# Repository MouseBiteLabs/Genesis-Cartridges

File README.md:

# Genesis-Cartridges
A collection of Genesis/Mega Drive cartridge circuit boards

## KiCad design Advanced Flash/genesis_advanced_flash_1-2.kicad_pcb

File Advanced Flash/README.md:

# Genesis / Mega Drive Advanced Flash Cart

This is a Sega Genesis/Mega Drive cartridge circuit board design that is capable of being flashed via the <a href="https://github.com/sanni/cartreader">Open Source Cart Reader (OSCR) by sanni</a>. Alternatively, you can also flash the ROM chips before soldering them to the board through the use of a programmer like the <a href="https://xgecu.myshopify.com/products/xgecu-new-t48-tl866-3gprogrammer-v12-01-support-28000-ics-for-spi-nor-nand-flash-emmc-bga153-162-169-100-221-tsop-sop-plcc">T48 programmer</a> with the <a href="https://xgecu.myshopify.com/products/100-original-xgecu-adp_f48_ex-1-tsop48-special-adapter-for-nor-flash-only-use-on-t48-tl866-3g-programmer">TSOP48 adapter</a>. This cartridge is made entirely from **brand new off the shelf components.** No donors are required, and you don't need to rely on AliExpress or eBay for parts!

This cartridge covers over 95% of the entire Genesis library. You can backup games up to 4 MB in size, with up to 32 KB RAM. It can also handle any ROM hack that falls into these limits, including the ever popular <a href="https://info.sonicretro.org/Sonic_3_Complete">Sonic 3 Complete</a>. Check out the <a href="https://github.com/MouseBiteLabs/Genesis-Cartridges/wiki/Game-Compatibility">Game Compatibility</a> page in the wiki for more info.

All gerbers and source files can be found in this repo, as this project is fully open source. Please read all instructions before attempting the project.

## Pending Version Update

Currently, v1.2 is available for download. It should operate exactly the same as v1.1, but I have not personally verified the new design yet as I have not ordered boards to try them out. The change to v1.2 is to allow these boards to be flashed with the OSCR as 32X cartridges, **but they will still be usable as regular Genesis/Mega Drive cartridges!** No new components have been added, it only needed a simple rewiring of an unused portion of U3.

I do not own a 32X to test this feature out, so if you would like to test out v1.2 for me with a 32X, feel free and let me know your results. Once I verify that my changes do not affect Genesis/Mega Drive compatibility (and they should not!) I will fully update everything here to assume v1.2 is the default version going forward.

For now, **v1.1 is perfectly acceptable for Genesis/Mega Drive games.**

## Important Things Before You Start

1) <a href="https://github.com/MouseBiteLabs/Genesis-Cartridges/wiki">Please review the wiki for more information about using the circuit boards, instructions for how to program them, and example builds.</a>
2) When soldering parts on, it's a good idea to put kapton tape or otherwise cover the bottom cartridge edge. You do not want to get solder on the cartridge contacts.
3) I am not responsible for any damage you do to your self or your property. Attempt this project at your own risk.
4) I do not guarantee design compatibility. You may encounter issues with certain games. There is also a chance I have made an error in the design or the BOM - if this is the case, I will do everything I can to address the problem as quickly as possible.
5) If you are using this board to make games other than for personal use, you must have permission from the originator to use and distribute any ROM images or other related material. You are responsible for making sure you adhere to any license requirements.

DO NOT use my circuit boards for profiting from stolen work - this especially includes homebrew content, ROM hacks, and using fan-made labels without permission from the originator. **Support ALL original creators!**

## Board Characteristics and Order Information

The zipped folder contains all the gerber files for this board. The following options **must** be chosen when ordering boards for yourself.

- Thickness: 1.6mm
- Surface Finish: ENIG
- Gold Fingers: Yes, 30° chamfer

You can use the zipped folder at any board fabricator you like. You may also buy the board from PCBWay using this link (disclosure: I receive 10% of the sale value to go towards future PCB orders of my own):

### Purchase from My Website

You can purchase this circuit board at my website, [https://mousebitelabs.store](https://mousebitelabs.store). Click the following image to be directed to the specific item listing:

### Purchase from Etsy

I also offer the board on Etsy, if you would rather purchase through there - click the banner to be redirected.

### Purchase from OSH Park

<a href="https://oshpark.com/shared_projects/HG0wx2nt">This board can also be ordered from OSH Park,</a> but you should sand down the edges of the cartridge to chamfer them yourself before inserting them in a console.

<a href="https://oshpark.com/shared_projects/83XjKdnh">Here is the OSH Park page for the untested v1.2 boards.</a>

<a href="https://www.retrorgb.com/determining-the-build-quality-of-a-game-cartridge.html">(Image taken from RetroRGB)</a>

## Required Equipment

- You will need basic tools, like a soldering iron, hot plate, and/or hot air rework station.
- You need a way to program the ROM chip(s).
  - This can be done with the <a href="https://github.com/sanni/cartreader">OSCR</a> to load the game and save data onto the catridge, after the cartridge is assembled.
  - Alternatively, the <a href="https://xgecu.myshopify.com/products/xgecu-new-t48-tl866-3gprogrammer-v12-01-support-28000-ics-for-spi-nor-nand-flash-emmc-bga153-162-169-100-221-tsop-sop-plcc">T48 programmer</a> with the <a href="https://xgecu.myshopify.com/products/100-original-xgecu-adp_f48_ex-1-tsop48-special-adapter-for-nor-flash-only-use-on-t48-tl866-3g-programmer">TSOP48 adapter</a> can program the ROM chip(s). The downside to this is that if you screw up the programming, you'll have to desolder the chips and program them again.

## How to Program

Please check out the wiki pages on how to prepare the ROM and program the cartridge.
- <a href="https://github.com/MouseBiteLabs/Genesis-Cartridges/wiki/Using-the-OSCR-%28Flash-Boards%29">Using the OSCR</a>
- <a href="https://github.com/MouseBiteLabs/Genesis-Cartridges/wiki/Using-the-T48-%28Flash-Boards%29">Using the T48</a>

## Board Configurations

You *may not* need every single part on this board to make a game. The game you want to make is mainly dependent on the ROM size and the RAM size (if any). Depending on your needs, you only need to solder on certain components, which you can find below in the BOM section.

- **Every board needs Group A components.** You can make games that have no RAM and are up to 2 MB large with this configuration.
- If you want to expand the ROM space to a full 4 MB, **add Group B components**.
- If you need RAM space, **add Group C components.** This will add 32 KB of RAM space.
- If your game is larger than 2 MB and uses any amount of SRAM, **add Group D components.**

<a href="https://github.com/MouseBiteLabs/Genesis-Cartridges/wiki/Advanced-Flash">Check out the wiki for visual examples.</a> If you want to have a fully functional board that you can configure for nearly every Genesis game, then populate all components (LEDs optional) and use the SPDT switch for SW1.

### Bypass Solder Jumpers

If your game is only 2 MB large, you will not need U3. There is a solder jumper inside the U3 footprint that needs to be bridged if this is the case.

Similarly, if your game does not use SRAM, you will not need U7 but you need to bridge the solder jumper instead.

### ROM Size Selection (SW1)

There is only one switch on this board for configuration purposes, and the setting you need to choose is pretty self-explanatory - **keep in mind, this is the size of the ROM file, *not* the amount of ROM space you have available on the board.** If you have both U1 and U2 populated, for example, but your ROM file is only 2 MB, you need to configure the board to the "less than or equal to 2 MB" setting.

You can either use an SPDT switch (part number shown in BOM below), or if you do not plan to reflash the board with a differently sized game in the future, you can hard-wire the selection. **This switch is only required to be configured if your board uses any amount of SRAM - ROM-only boards do not utilize this setting.**

In the image below, the "less than or equal to 2MB" option is selected in both cases. The resistor on the right is a zero-ohm jumper (or you can use a solder blob).

## Estimating Battery Life

To accurately estimate the battery life, you must first solder the battery in, and then either program your game in the OSCR or power it on in a console.

After that, measure the voltage across R1 (either on the part itself or on the + and - pads on the back of the board) using a multimeter in DC mV mode, touching the probes to the two test point pads on either side of R1. You should read something around 1 mV or less. If you are severely higher than 1 mV, like in the 10's of mV, then you have a problem on your board.

Once you have a suitable voltage, find the milliamp-hour rating of your selected battery (preferrably from a datasheet). For example, a Renata CR2032 battery is rated for 225 mAh.

Now to estimate battery life, take the voltage measurement in mV and the battery rating in mAh, and plug it into this equation: 

Time (years) = Resistance of R1 (ohms) * Battery capacity (mAh) / Voltage (mV) / 8760

The factor of 8760 is for converting years to hours (24 hours in a day, 365 days in a year). The resistance of R1 is 1000 ohms. So for an example, if you measured 1 mV on R1 and are using a Renata CR2032, you would get 1000 * 225 / 1 / 8760 = **25.7 years.**

## Bill of Materials (BOM)

The component groups required for the build you want to make are detailed above.

### Mouser Shopping Cart

The following cart has *the maximum amount* of parts you would potentially need on a single board, plus a few extras of the passive components due to price breaks. You can remove the chips you don't need from the shopping cart before ordering, according to the component group assignments below.

https://www.mouser.com/ProjectManager/ProjectDetail.aspx?AccessID=ea748d2d57

### Group A - 2 MB ROM, No RAM

| Reference | Value/Part Number | Package | Description      | Source                                           |
| --------- | ----------------- | ------- | ---------------- | ------------------------------------------------ |
| C1        | 0.1uF             | 0603    | Capacitor (MLCC) | [https://mou.sr/3ENc15O](https://mou.sr/3ENc15O) |
| CC        | 22uF              | 1206    | Capacitor (MLCC) | [https://mou.sr/4e4zShm](https://mou.sr/4e4zShm) |
| U1        | M29F160           | TSOP-48 | Flash EEPROM     | [https://mou.sr/3HIjb09](https://mou.sr/3HIjb09) |

### Group B - Adds 2 MB of ROM

| Reference | Value/Part Number | Package  | Description      | Source                                           |
| --------- | ----------------- | -------- | ---------------- | ------------------------------------------------ |
| C2        | 0.1uF             | 0603     | Capacitor (MLCC) | [https://mou.sr/3ENc15O](https://mou.sr/3ENc15O) |
| C3        | 0.1uF             | 0603     | Capacitor (MLCC) | [https://mou.sr/3ENc15O](https://mou.sr/3ENc15O) |
| U2        | M29F160           | TSOP-48  | Flash EEPROM     | [https://mou.sr/3HIjb09](https://mou.sr/3HIjb09) |
| U3        | 74HCT139          | TSSOP-16 | Decoder          | [https://mou.sr/4eqzppn](https://mou.sr/4eqzppn) |

### Group C - Adds 32 KB of RAM for games with 2 MB of ROM or less in size

| Reference | Value/Part Number | Package  | Description        | Source                                           |
| --------- | ----------------- | -------- | ------------------ | ------------------------------------------------ |
| B1        | CR2032            | CR2032   | Coin Cell Battery  | [https://mou.sr/3Wj2m0G](https://mou.sr/3Wj2m0G) |
| C4        | 0.1uF             | 0603     | Capacitor (MLCC)   | [https://mou.sr/3ENc15O](https://mou.sr/3ENc15O) |
| C5        | 0.1uF             | 0603     | Capacitor (MLCC)   | [https://mou.sr/3ENc15O](https://mou.sr/3ENc15O) |
| C7        | 0.1uF             | 0603     | Capacitor (MLCC)   | [https://mou.sr/3ENc15O](https://mou.sr/3ENc15O) |
| CB        | 22uF              | 1206     | Capacitor (MLCC)   | [https://mou.sr/4e4zShm](https://mou.sr/4e4zShm) |
| R1        | 1k                | 0603     | Resistor           | [https://mou.sr/3U0EvS4](https://mou.sr/3U0EvS4) |
| R2        | 130k              | 0603     | Resistor           | [https://mou.sr/3MjXliy](https://mou.sr/3MjXliy) |
| R3        | 49.9k             | 0603     | Resistor           | [https://mou.sr/3BBcDgp](https://mou.sr/3BBcDgp) |
| U4        | AS6C62256         | SOP-28   | SRAM               | [https://mou.sr/4oDz7Bu](https://mou.sr/4oDz7Bu) |
| U5        | TPS3613           | MSOP-10  | Battery Management | [https://mou.sr/45Ir2kh](https://mou.sr/45Ir2kh) |
| U7        | 74HCT139          | TSSOP-16 | Decoder            | [https://mou.sr/4eqzppn](https://mou.sr/4eqzppn) |

### Group D - Adds capability for larger games to utilize RAM

| Reference | Value/Part Number | Package   | Description      | Source                                           |
| --------- | ----------------- | --------- | ---------------- | ------------------------------------------------ |
| C6        | 0.1uF             | 0603      | Capacitor (MLCC) | [https://mou.sr/3ENc15O](https://mou.sr/3ENc15O) |
| SW1       | CAS-120B          | Gull-wing | SPDT Switch      | [https://mou.sr/4fCZDqy](https://mou.sr/4fCZDqy) |
| U6        | 74HCT74           | TSSOP-14  | Flip Flop        | [https://mou.sr/4mKwqfF](https://mou.sr/4mKwqfF) |

Note: SW1 is optional and can be replaced with solder bridges or zero ohm resistors.

## Adding LEDs

There are 10 spots around the border of the board on the front and back for LEDs. This includes pads for an 0603 size resistor and 0603 size LED, powered by the 5V rail. Resistor and LED selection will vary based on your own preferences, so you will have to experiment with values yourself.

### LED fix for v1.0

Four of the current limiting resistors for the LEDs are missing a connection to +5V on the board. Luckily, mirrored on the very opposite side of the board, there is a +5V point for each of the four resistors. You can use short jumpers to connect the front resistors to the back resistors in the following locations to make the LEDs light up:

## Revision History

### v1.2

- Added compatibility for flashing 32X games via the OSCR

### v1.1 - Release

- Fix LED resistor connections on the back of the board
- Added test points for measuring battery current easier

### v1.0 - Alpha

- Prototype version

## Acknowledgements

- Huge thanks to sanni for firstly creating the OSCR, and secondly for adding programming support for the cartridges.
- Additionally huge thanks to agi from the discord community for his work on adding flash support for these boards to the OSCR! You have made this cartridge so much better through your hard work.
- ANOTHER thanks to agi for figuring out 32X compatibility required for v1.2.
- Continual thanks to all in the nesdev community for their resources, design tips, and support throughout the past half-decade.

## License

<br />This work is licensed under a <a rel="license" href="http://creativecommons.org/licenses/by-sa/4.0/">Creative Commons Attribution-ShareAlike 4.0 International License</a>. You are able to copy and redistribute the material in any medium or format, as well as remix, transform, or build upon the material for any purpose (even commercial) - but you **must** give appropriate credit, provide a link to the license, and indicate if any changes were made.

©MouseBiteLabs 2025

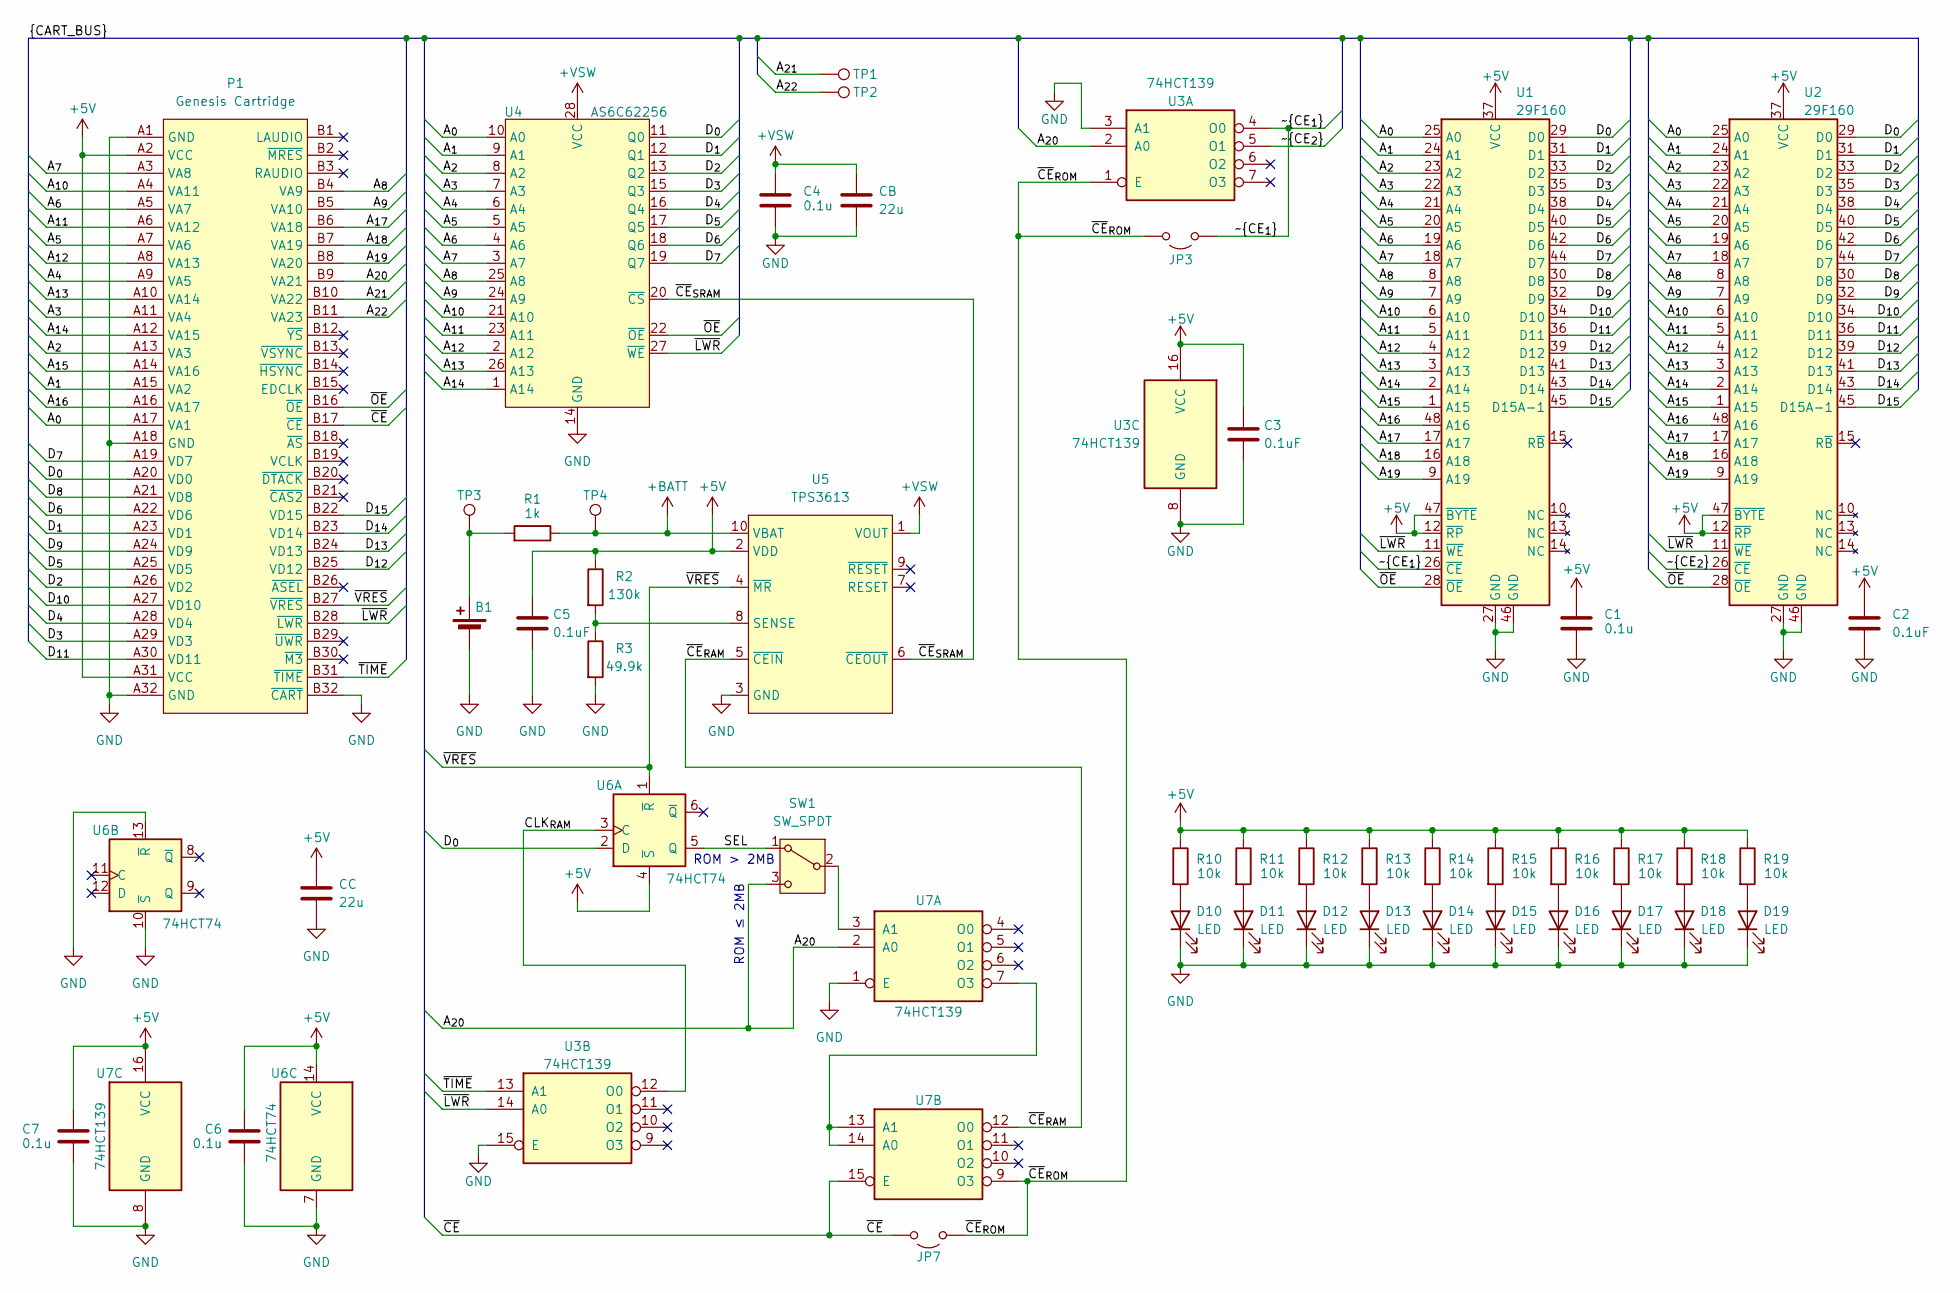
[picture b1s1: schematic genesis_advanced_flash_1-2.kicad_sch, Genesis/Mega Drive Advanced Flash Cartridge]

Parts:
B1: CR2025; COIN_CELL
C1, C4, C6, C7: 0.1u; C_0603_1608Metric_Boxed
C2, C3, C5: 0.1uF; C_0603_1608Metric_Boxed
CB: 22u; C_1206_3216Metric_Boxed
CC: 22u; C_1206_3216Metric_Boxed
D10, D11, D12, D13, D14, D15, D16, D17, D18, D19: LED; LED_0603_1608Metric_Pad1.05x0.95mm_HandSolder
JP3, JP7: Jumper_2_Open; SJ
P1: Genesis Cartridge; GENESIS_CART
R1: 1k; R_0603_1608Metric_Boxed
R2: 130k; R_0603_1608Metric_Boxed
R3: 49.9k; R_0603_1608Metric_Boxed
R10, R11, R12, R13, R14, R15, R16, R17, R18, R19: 10k; R_0603_1608Metric_Boxed
SW1: SW_SPDT; CAS120B
TP1, TP2, TP3, TP4: TPB1,27; TestPoint_Pad_D1.0mm
U1, U2: 29F160; TSOP-I-48_18.4x12mm_P0.5mm
U3, U7: 74HCT139; TSSOP-16_4.4x5mm_P0.65mm
U4: AS6C62256; SO28
U5: TPS3613; MSOP-10_3x3mm_P0.5mm
U6: 74HCT74; TSSOP-14_4.4x5mm_P0.65mm

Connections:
+5V: C1.1, C2.1, C3.1, C5.1, C6.1, C7.1, CC.1, P1.A2 (VCC), P1.A31 (VCC), R2.1, R10.1, R11.1, R12.1, R13.1, R14.1, R15.1, R16.1, R17.1, R18.1, R19.1, U1.12 (~RP), U1.37 (VCC), U1.47 (~BYTE), U2.12 (~RP), U2.37 (VCC), U2.47 (~BYTE), U3.16 (VCC), U5.2 (VDD), U6.4 (~S), U6.14 (VCC), U7.16 (VCC)
+BATT: R1.1, TP4.1, U5.10 (VBAT)
+VSW: C4.1, CB.1, U4.28 (VCC), U5.1 (VOUT)
/A_{0}: P1.A17 (VA1), U1.25 (A0), U2.25 (A0), U4.10 (A0)
/A_{1}: P1.A15 (VA2), U1.24 (A1), U2.24 (A1), U4.9 (A1)
/A_{2}: P1.A13 (VA3), U1.23 (A2), U2.23 (A2), U4.8 (A2)
/A_{3}: P1.A11 (VA4), U1.22 (A3), U2.22 (A3), U4.7 (A3)
/A_{4}: P1.A9 (VA5), U1.21 (A4), U2.21 (A4), U4.6 (A4)
/A_{5}: P1.A7 (VA6), U1.20 (A5), U2.20 (A5), U4.5 (A5)
/A_{6}: P1.A5 (VA7), U1.19 (A6), U2.19 (A6), U4.4 (A6)
/A_{7}: P1.A3 (VA8), U1.18 (A7), U2.18 (A7), U4.3 (A7)
/A_{8}: P1.B4 (VA9), U1.8 (A8), U2.8 (A8), U4.25 (A8)
/A_{9}: P1.B5 (VA10), U1.7 (A9), U2.7 (A9), U4.24 (A9)
/A_{10}: P1.A4 (VA11), U1.6 (A10), U2.6 (A10), U4.21 (A10)
/A_{11}: P1.A6 (VA12), U1.5 (A11), U2.5 (A11), U4.23 (A11)
/A_{12}: P1.A8 (VA13), U1.4 (A12), U2.4 (A12), U4.2 (A12)
/A_{13}: P1.A10 (VA14), U1.3 (A13), U2.3 (A13), U4.26 (A13)
/A_{14}: P1.A12 (VA15), U1.2 (A14), U2.2 (A14), U4.1 (A14)
/A_{15}: P1.A14 (VA16), U1.1 (A15), U2.1 (A15)
/A_{16}: P1.A16 (VA17), U1.48 (A16), U2.48 (A16)
/A_{17}: P1.B6 (VA18), U1.17 (A17), U2.17 (A17)
/A_{18}: P1.B7 (VA19), U1.16 (A18), U2.16 (A18)
/A_{19}: P1.B8 (VA20), U1.9 (A19), U2.9 (A19)
/A_{20}: P1.B9 (VA21), SW1.3 (C), U3.2 (A0), U7.2 (A0)
/A_{21}: P1.B10 (VA22), TP1.1
/A_{22}: P1.B11 (VA23), TP2.1
/CLK_{RAM}: U3.12 (O0), U6.3 (C)
/D_{0}: P1.A20 (VD0), U1.29 (D0), U2.29 (D0), U4.11 (Q0), U6.2 (D)
/D_{1}: P1.A23 (VD1), U1.31 (D1), U2.31 (D1), U4.12 (Q1)
/D_{2}: P1.A26 (VD2), U1.33 (D2), U2.33 (D2), U4.13 (Q2)
/D_{3}: P1.A29 (VD3), U1.35 (D3), U2.35 (D3), U4.15 (Q3)
/D_{4}: P1.A28 (VD4), U1.38 (D4), U2.38 (D4), U4.16 (Q4)
/D_{5}: P1.A25 (VD5), U1.40 (D5), U2.40 (D5), U4.17 (Q5)
/D_{6}: P1.A22 (VD6), U1.42 (D6), U2.42 (D6), U4.18 (Q6)
/D_{7}: P1.A19 (VD7), U1.44 (D7), U2.44 (D7), U4.19 (Q7)
/D_{8}: P1.A21 (VD8), U1.30 (D8), U2.30 (D8)
/D_{9}: P1.A24 (VD9), U1.32 (D9), U2.32 (D9)
/D_{10}: P1.A27 (VD10), U1.34 (D10), U2.34 (D10)
/D_{11}: P1.A30 (VD11), U1.36 (D11), U2.36 (D11)
/D_{12}: P1.B25 (VD12), U1.39 (D12), U2.39 (D12)
/D_{13}: P1.B24 (VD13), U1.41 (D13), U2.41 (D13)
/D_{14}: P1.B23 (VD14), U1.43 (D14), U2.43 (D14)
/D_{15}: P1.B22 (VD15), U1.45 (D15A-1), U2.45 (D15A-1)
/SEL: SW1.1 (A), U6.5 (Q)
/~CE_{1}: JP3.2 (B), U1.26 (~CE), U3.4 (O0)
/~CE_{2}: U2.26 (~CE), U3.5 (O1)
/~CE: JP7.1 (A), P1.B17 (~CE), U7.15 (E)
/~CE_{RAM}: U5.5 (~CEIN), U7.12 (O0)
/~CE_{ROM}: JP3.1 (A), JP7.2 (B), U3.1 (E), U7.9 (O3)
/~CE_{SRAM}: U4.20 (~CS), U5.6 (~CEOUT)
/~LWR: P1.B28 (~LWR), U1.11 (~WE), U2.11 (~WE), U3.14 (A0), U4.27 (~WE)
/~OE: P1.B16 (~OE), U1.28 (~OE), U2.28 (~OE), U4.22 (~OE)
/~TIME: P1.B31 (~TIME), U3.13 (A1)
/~VRES: P1.B27 (~VRES), U5.4 (~MR), U6.1 (~R)
GND: B1.2 (-), C1.2, C2.2, C3.2, C4.2, C5.2, C6.2, C7.2, CB.2, CC.2, D10.1 (K), D11.1 (K), D12.1 (K), D13.1 (K), D14.1 (K), D15.1 (K), D16.1 (K), D17.1 (K), D18.1 (K), D19.1 (K), P1.A1 (GND), P1.A18 (GND), P1.A32 (GND), P1.B32 (~CART), R3.2, U1.27 (GND), U1.46 (GND), U2.27 (GND), U2.46 (GND), U3.3 (A1), U3.8 (GND), U3.15 (E), U4.14 (GND), U5.3 (GND), U6.7 (GND), U6.10 (~S), U6.13 (~R), U7.1 (E), U7.8 (GND)
unnamed: B1.1 (+), R1.2, TP3.1
unnamed: D10.2 (A), R10.2
unnamed: D11.2 (A), R11.2
unnamed: D12.2 (A), R12.2
unnamed: D13.2 (A), R13.2
unnamed: D14.2 (A), R14.2
unnamed: D15.2 (A), R15.2
unnamed: D16.2 (A), R16.2
unnamed: D17.2 (A), R17.2
unnamed: D18.2 (A), R18.2
unnamed: D19.2 (A), R19.2
unnamed: SW1.2 (B), U7.3 (A1)
unnamed: R2.2, R3.1, U5.8 (SENSE)
unnamed: U7.7 (O3), U7.13 (A1), U7.14 (A0)

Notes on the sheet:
ROM ≤ 2MB
ROM > 2MB

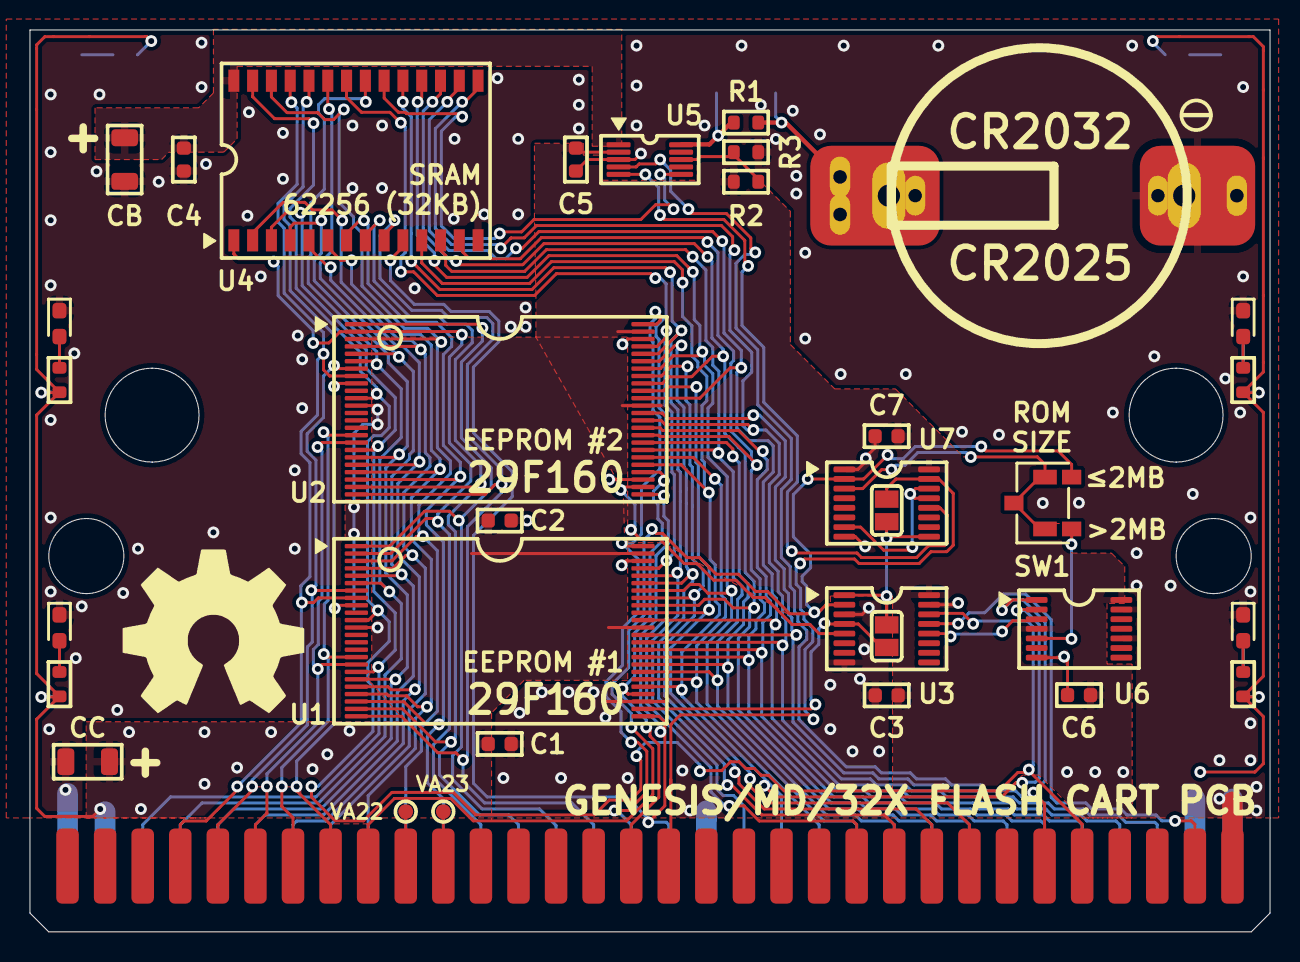
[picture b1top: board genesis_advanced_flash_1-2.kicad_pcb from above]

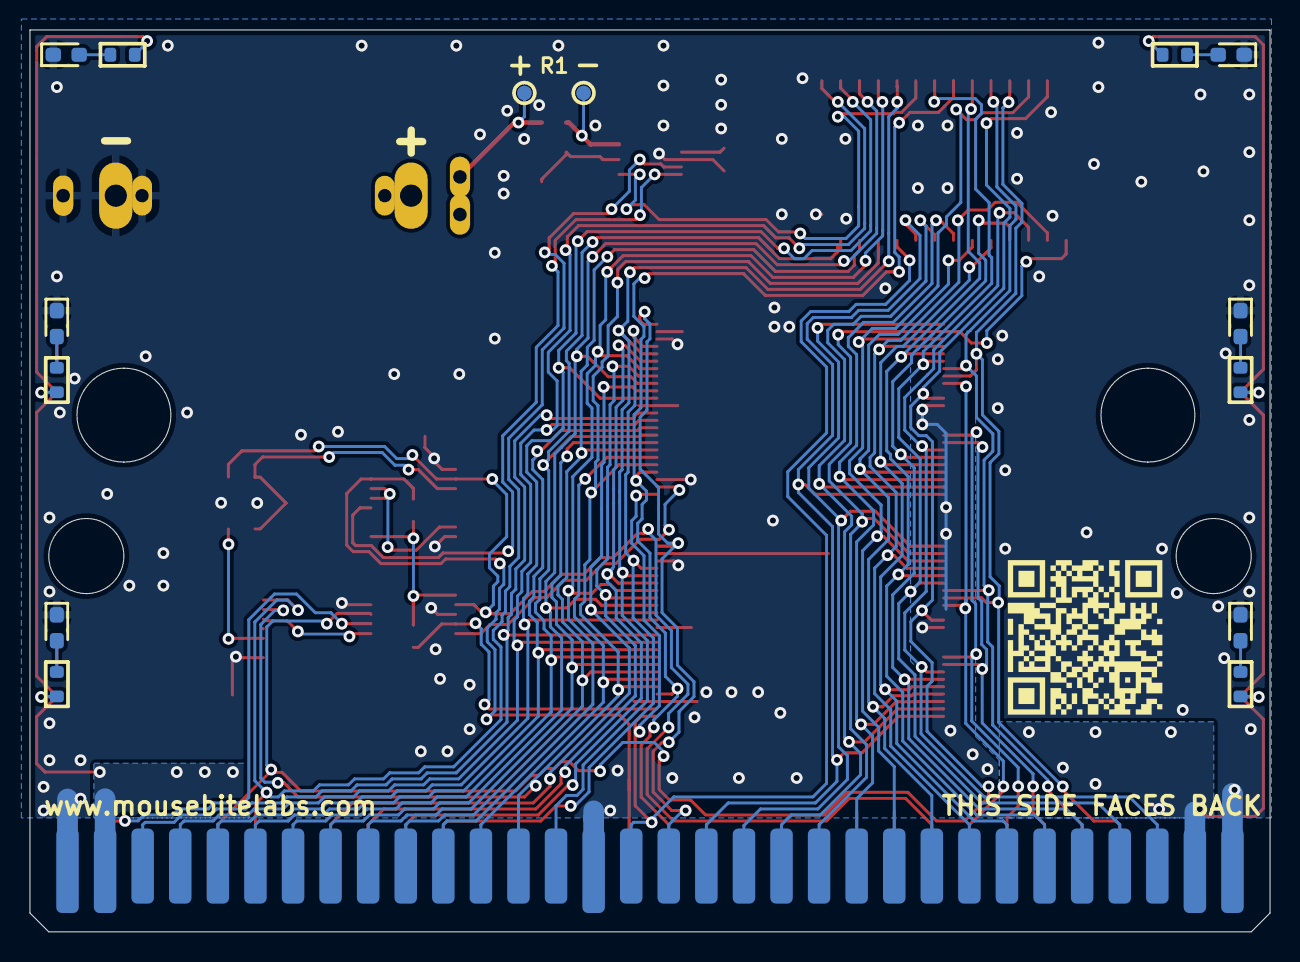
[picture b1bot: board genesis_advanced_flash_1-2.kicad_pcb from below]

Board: 2 copper layers, 83.8 x 61.0 mm, 48 parts (14 on the bottom side), 69 nets.

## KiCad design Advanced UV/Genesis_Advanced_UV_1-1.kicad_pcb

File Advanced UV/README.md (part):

# Genesis / Mega Drive Advanced UV Cart - UNDER CONSTRUCTION

# Order at your own risk. These are technically untested.

This is a Sega Genesis/Mega Drive cartridge circuit board design that uses the older UV EPROMs, 27C322 or 27C160. This is the updated version of my existing carts, ported from Eagle to KiCad with some minor changes, but fully open source. With this board, unlike the flash version, you need to program the EPROM before soldering to the board. This cartridge is made entirely from **off the shelf components.** No donors are required.

This cartridge covers over 95% of the entire Genesis library. You can backup games up to 4 MB in size, with up to 32 KB RAM. It can also handle any ROM hack that falls into these limits, including the ever popular <a href="https://info.sonicretro.org/Sonic_3_Complete">Sonic 3 Complete</a>. Check out the <a href="https://github.com/MouseBiteLabs/Genesis-Cartridges/wiki/Game-Compatibility">Game Compatibility</a> page in the wiki for more info.

All gerbers and source files can be found in this repo, as this project is fully open source. Please read all instructions before attempting the project.

## Important Things Before You Start

1) <a href="https://github.com/MouseBiteLabs/Genesis-Cartridges/wiki">Please review the wiki for more information about using the circuit boards, instructions for how to program them, and example builds.</a>
2) When soldering parts on, it's a good idea to put kapton tape or otherwise cover the bottom cartridge edge. You do not want to get solder on the cartridge contacts.
3) I am not responsible for any damage you do to your self or your property. Attempt this project at your own risk.
4) I do not guarantee design compatibility. You may encounter issues with certain games. There is also a chance I have made an error in the design or the BOM - if this is the case, I will do everything I can to address the problem as quickly as possible.
5) If you are using this board to make games other than for personal use, you must have permission from the originator to use and distribute any ROM images or other related material. You are responsible for making sure you adhere to any license requirements.

DO NOT use my circuit boards for profiting from stolen work - this especially includes homebrew content, ROM hacks, and using fan-made labels without permission from the originator. **Support ALL original creators!**

## Board Characteristics and Order Information

The zipped folder contains all the gerber files for this board. The following options **must** be chosen when ordering boards for yourself.

- Thickness: 1.6mm
- Surface Finish: ENIG
- Gold Fingers: Yes, 30° chamfer

You can use the zipped folder at any board fabricator you like. You may also buy the board from PCBWay using this link (disclosure: I receive 10% of the sale value to go towards future PCB orders of my own):

### Purchase from My Website

You can purchase this circuit board at my website, [https://mousebitelabs.store](https://mousebitelabs.store). Click the following image to be directed to the specific item listing:

### Purchase from Etsy

I also offer the board on Etsy, if you would rather purchase through there - click the banner to be redirected.

### Purchase from OSH Park

<a href="https://oshpark.com/shared_projects/QJOp6D4P">This board can also be ordered from OSH Park,</a> but you should sand down the edges of the cartridge to chamfer them yourself before inserting them in a console.

<a href="https://www.retrorgb.com/determining-the-build-quality-of-a-game-cartridge.html">(Image taken from RetroRGB)</a>

## Required Equipment

- You will need basic tools and supplies, like a soldering iron, solder, and flux.
- You need a way to program the ROM chip(s). There are two ways I have programmed them in the past:
  - Using the <a href="https://xgecu.myshopify.com/products/xgecu-new-t48-tl866-3gprogrammer-v12-01-support-28000-ics-for-spi-nor-nand-flash-emmc-bga153-162-169-100-221-tsop-sop-plcc">T48 programmer</a> with my <a href="https://github.com/MouseBiteLabs/27C322-TL866-Adapter">27C322 to TL866 Programming Adatper</a> board. The programming adapter is compatible with the T48, and it allows you to program the 42-pin EPROMs (27C160 and 27C322) with the 40-pin T48 programmer.
  OR
  - Using the <a href="https://www.mcumall.com/store/index.php?route=product/product&path=66&product_id=85">GQ4x4 programmer</a> with the ZIF adapter board that comes with it.

## How to Program

<a href="https://github.com/MouseBiteLabs/Genesis-Cartridges/wiki/Programming-UV-EPROMs">Please check out the wiki pages on how to prepare the ROM and program the cartridge.</a>

## Board Configurations

You *may not* need every single part on this board to make a game. The game you want to make is mainly dependent on the ROM size and the RAM size (if any). Depending on your needs, you only need to solder on certain components, which you can find below in the BOM section.

- **Every board needs Group A components.** You can make games that have no RAM and are up to 4 MB large with this configuration.
- If you need RAM space, **add Group C components.** This will add 32 KB of RAM space.
- If your game is larger than 2 MB and uses any amount of SRAM, **add Group D components.**

<a href="https://github.com/MouseBiteLabs/Genesis-Cartridges/wiki/Advanced-UV">Check out the wiki for visual examples.</a>

### Picking an EPROM, and ROM Size Selection Pads

If your game is only 2 MB large or less, you can use a 27C160. If your game is larger than 2 MB (but 4 MB or less), then you need to use a 27C322. These parts are only available second-hand on places like AliExpress or eBay.

The setting you need to choose for these jumpers is pretty self-explanatory - **keep in mind, this is the size of the ROM file, *not* the amount of ROM space you have available on the board.** If you have a 27C322, for example, but your ROM file is only 2 MB, you need to configure the board to the "less than or equal to 2 MB" setting. Also, these pads are only required to be configured if your board uses any amount of SRAM - ROM-only boards do not utilize this setting (but it won't hurt to solder the proper selection anyway).

### Bypass Solder Jumper

If your game does not use SRAM, you will not need U4 but you need to bridge the solder jumper instead.

## Estimating Battery Life

Measure the voltage across R1 using a multimeter in DC mV mode, touching the probes to either the leads on R1 or the pads on the back of the board for R1. You should read something around 1 mV or less. If you are severely higher than 1 mV, like in the 10's of mV, then you have a problem on your board.

Once you have a suitable voltage, find the milliamp-hour rating of your selected battery (preferrably from a datasheet). For example, a Renata CR2032 battery is rated for 225 mAh.

Now to estimate battery life, take the voltage measurement in mV and the battery rating in mAh, and plug it into this equation: 

Time (years) = Resistance of R1 (ohms) * Battery capacity (mAh) / Voltage (mV) / 8760

The factor of 8760 is for converting years to hours (24 hours in a day, 365 days in a year). The resistance of R1 is 1000 ohms. So for an example, if you measured 1 mV on R1 and are using a Renata CR2032, you would get 1000 * 225 / 1 / 8760 = **25.7 years.**

## Bill of Materials (BOM)

The component groups required for the build you want to make are detailed above.

### Mouser Shopping Cart

The following cart has *the maximum amount* of parts you would potentially need on a single board, plus a few extras of the passive components due to price breaks. You can remove the chips you don't need from the shopping cart before ordering, according to the component group assignments below. **This cart does not include the UV EPROM you will need, as they are not available on Mouser.**

https://www.mouser.com/ProjectManager/ProjectDetail.aspx?AccessID=e4c93a8a57

The parts in this cart are for the through-hole versions of the parts, but there are pads if you want to use surface mount instead for the resistors, capacitors, diodes, and transistor.

### Group A - Up to 4 MB ROM, No RAM

| Reference | Value/Part Number | Package       | Description                     | Source                      |
| --------- | ----------------- | ------------- | ------------------------------- | --------------------------- |
| C1        | 0.1uF             | 5mm spacing   | Capacitor (MLCC)                | https://mou.sr/4mvAwIR      |
| CC        | 22uF              | 5mm x 5mm     | Aluminum Electrolytic Capacitor | https://mou.sr/4moiXKK      |
| U1        | 27C160 / 27C322   | DIP-42        | UV EPROM                        | Search on Aliexpress, eBay  |

### Group C - Adds 32 KB of RAM for games with 2 MB of ROM or less in size

| Reference | Value/Part Number | Package  | Description                     | Source                  |
| --------- | ----------------- | -------- | ------------------------------- | ----------------------- |
| B1        | CR2032       | CR2032        | Coin Cell Battery               | https://mou.sr/3Wj2m0G  |
| C2        | 0.1uF        | 5mm spacing   | Capacitor (MLCC)                | https://mou.sr/4mvAwIR  |
| C4        | 0.1uF        | 5mm spacing   | Capacitor (MLCC)                | https://mou.sr/4mvAwIR  |
| CB        | 22uF         | 5mm x 5mm     | Aluminum Electrolytic Capacitor | https://mou.sr/4moiXKK  |
| D1        | BAT85        | DO-35-2       | Diode                           | https://mou.sr/49GVT4m  |
| D2        | BAT85        | DO-35-2       | Diode                           | https://mou.sr/49GVT4m  |
| D3        | BAT85        | DO-35-2       | Diode                           | https://mou.sr/49GVT4m  |
| Q1        | 2N3904       | TO-92-3       | Transistor (NPN)                | https://mou.sr/43xUgCR  |
| R1        | 1k           | Axial, 3.3mm  | Resistor                        | https://mou.sr/4lIm13d  |
| R2        | 100k         | Axial, 3.3mm  | Resistor                        | https://mou.sr/3NOD0De  |
| R3        | 10k          | Axial, 3.3mm  | Resistor                        | https://mou.sr/4kr1K2t  |
| R4        | 1k           | Axial, 3.3mm  | Resistor                        | https://mou.sr/4lIm13d  |
| R5        | 10k          | Axial, 3.3mm  | Resistor                        | https://mou.sr/4kr1K2t  |
| U2        | AS6C62256    | DIP-28        | SRAM                            | https://mou.sr/3HlZ0mh  |
| U4        | 74HCT139     | DIP-16        | Decoder                         | https://mou.sr/441VXuJ  |

### Group D - Adds capability for larger games to utilize RAM

| Reference | Value/Part Number | Package   | Description      | Source                                           |
| --------- | ----------------- | --------- | ---------------- | ------------------------------------------------ |
| C3        | 0.1uF             | 5mm spacing   | Capacitor (MLCC) | https://mou.sr/4mvAwIR                       |
| U3        | 74HCT74           | DIP-14        | Flip-Flop        | https://mou.sr/3YEiVo8                       |

## Adding LEDs

There are 10 spots around the border of the board on the front and back for LEDs. This includes pads for an 0603 size resistor and 0603 size LED, powered by the 5V rail. Resistor and LED selection will vary based on your own preferences, so you will have to experiment with values yourself.

## Revision History

### v1.1 - Release

- Fixed /WR hole location to not overlap silkscreen

### v1.0 - Alpha

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
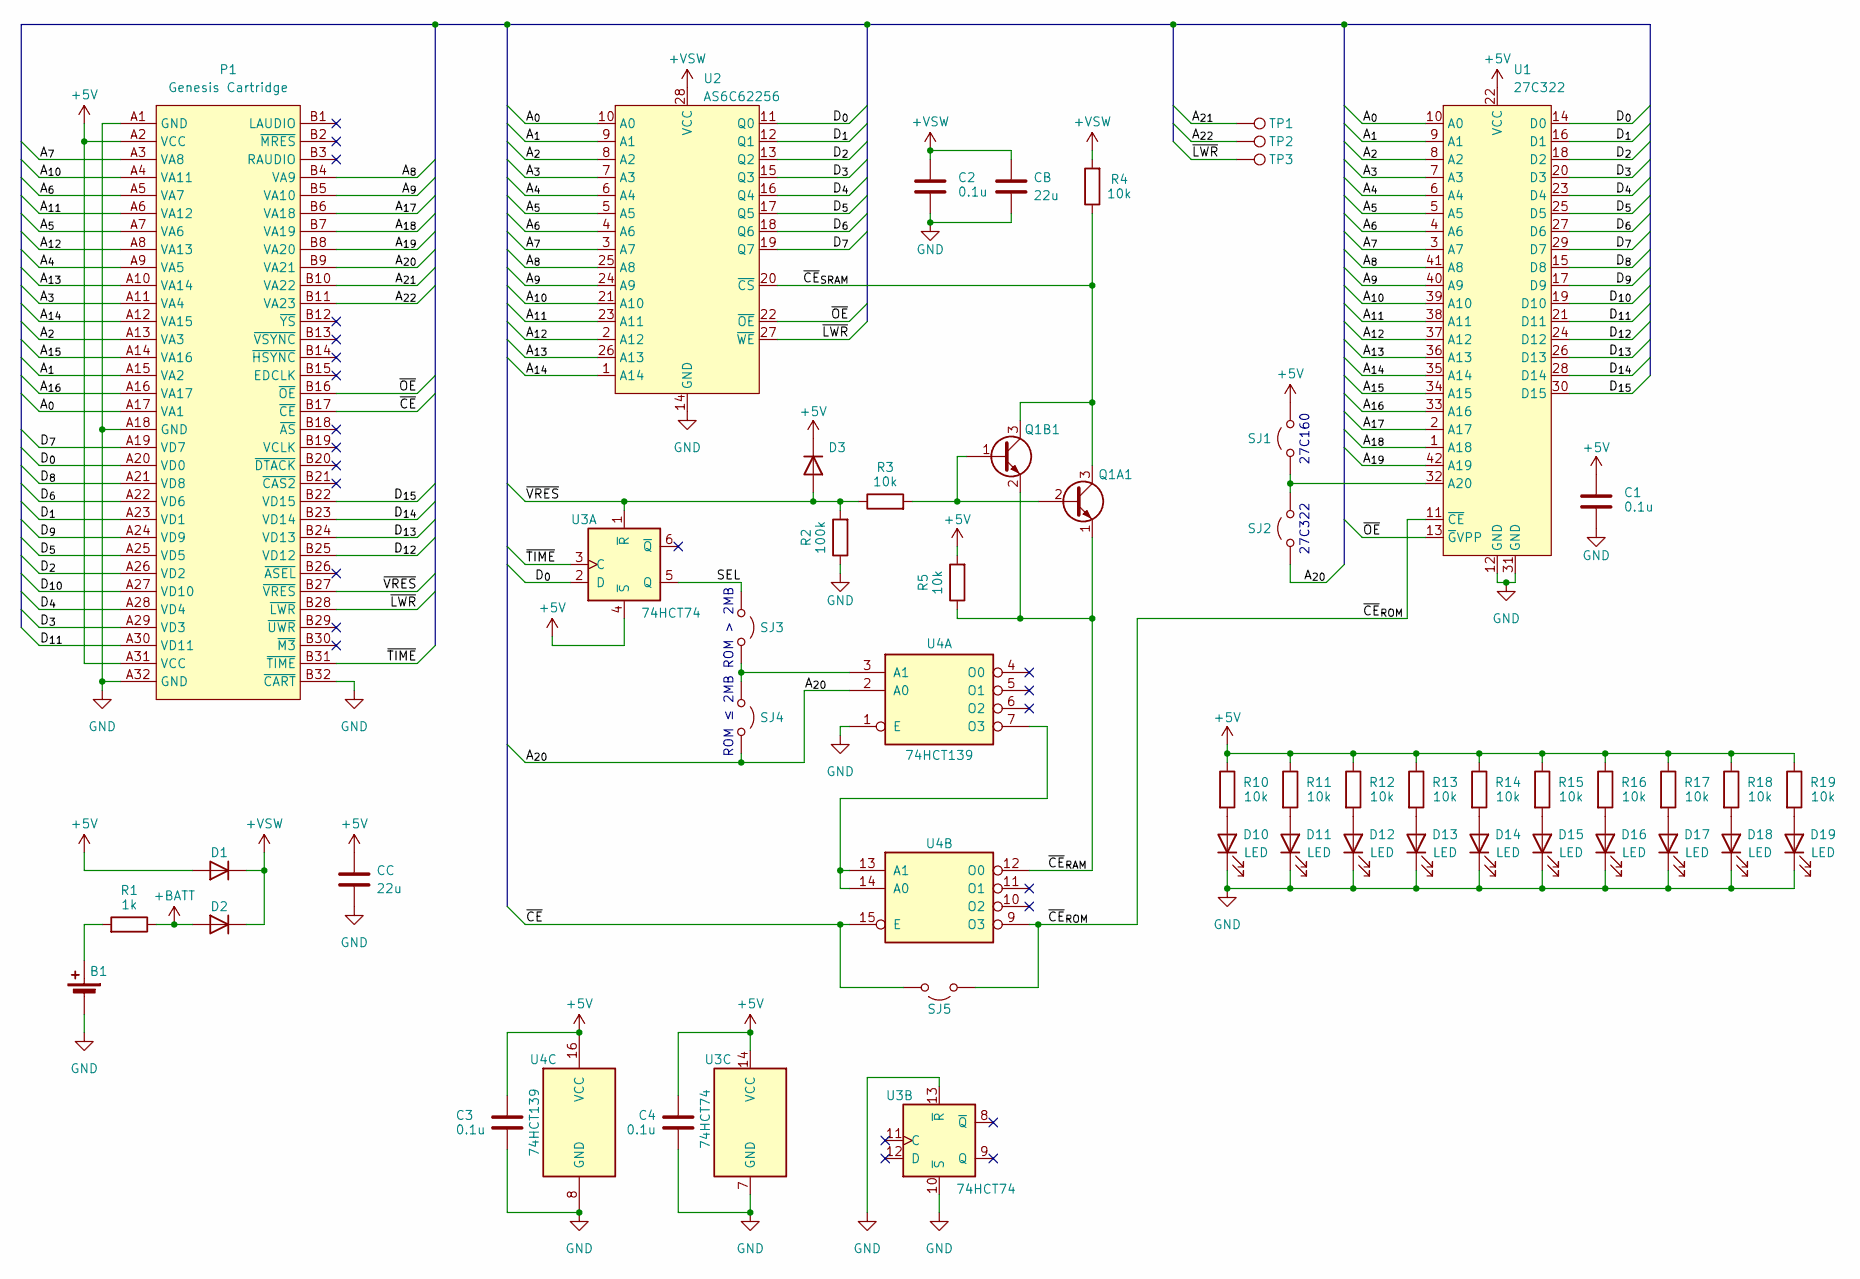
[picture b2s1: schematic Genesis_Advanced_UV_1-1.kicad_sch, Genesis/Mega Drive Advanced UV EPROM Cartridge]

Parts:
B1: CR2025; COIN_CELL
C1, C2, C3, C4: 0.1u; THT_SMT_0803_SHORT
CB: 22u; CP_Radial_D5.0mm_P2.50mm
CC: 22u; CP_Radial_D5.0mm_P2.50mm
D1, D2, D3: D; DIODE_THT_SMT
D10, D11, D12, D13, D14, D15, D16, D17, D18, D19: LED; LED_0603_1608Metric_Pad1.05x0.95mm_HandSolder
P1: Genesis Cartridge; GENESIS_CART
Q1A1: 2N3904; TO-92L_Inline_Wide
Q1B1: MMBT3904; SOT-23
R1: 1k; THT_SMT_0803
R2: 100k; THT_SMT_0803
R3, R4, R5: 10k; THT_SMT_0803
R10, R11, R12, R13, R14, R15, R16, R17, R18, R19: 10k; R_0603_1608Metric_Boxed
SJ1, SJ2, SJ3, SJ4, SJ5: Jumper_2_Open; SJ
TP1, TP2, TP3: TPB1,27; TestPoint_THTPad_D1.5mm_Drill0.7mm
U1: 27C322; DIP-42_W15.24mm
U2: AS6C62256; DIP-28_W15.24mm_DUAL
U3: 74HCT74; DIP-14_W7.62mm
U4: 74HCT139; DIP-16_W7.62mm

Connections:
+5V: C1.1, C3.1, C4.1, CC.1, D1.2 (A), D3.1 (K), P1.A2 (VCC), P1.A31 (VCC), R5.2, R10.1, R11.1, R12.1, R13.1, R14.1, R15.1, R16.1, R17.1, R18.1, R19.1, SJ1.2 (B), U1.22 (VCC), U3.4 (~S), U3.14 (VCC), U4.16 (VCC)
+BATT: D2.2 (A), R1.1
+VSW: C2.1, CB.1, D1.1 (K), D2.1 (K), R4.2, U2.28 (VCC)
/A_{0}: P1.A17 (VA1), U1.10 (A0), U2.10 (A0)
/A_{1}: P1.A15 (VA2), U1.9 (A1), U2.9 (A1)
/A_{2}: P1.A13 (VA3), U1.8 (A2), U2.8 (A2)
/A_{3}: P1.A11 (VA4), U1.7 (A3), U2.7 (A3)
/A_{4}: P1.A9 (VA5), U1.6 (A4), U2.6 (A4)
/A_{5}: P1.A7 (VA6), U1.5 (A5), U2.5 (A5)
/A_{6}: P1.A5 (VA7), U1.4 (A6), U2.4 (A6)
/A_{7}: P1.A3 (VA8), U1.3 (A7), U2.3 (A7)
/A_{8}: P1.B4 (VA9), U1.41 (A8), U2.25 (A8)
/A_{9}: P1.B5 (VA10), U1.40 (A9), U2.24 (A9)
/A_{10}: P1.A4 (VA11), U1.39 (A10), U2.21 (A10)
/A_{11}: P1.A6 (VA12), U1.38 (A11), U2.23 (A11)
/A_{12}: P1.A8 (VA13), U1.37 (A12), U2.2 (A12)
/A_{13}: P1.A10 (VA14), U1.36 (A13), U2.26 (A13)
/A_{14}: P1.A12 (VA15), U1.35 (A14), U2.1 (A14)
/A_{15}: P1.A14 (VA16), U1.34 (A15)
/A_{16}: P1.A16 (VA17), U1.33 (A16)
/A_{17}: P1.B6 (VA18), U1.2 (A17)
/A_{18}: P1.B7 (VA19), U1.1 (A18)
/A_{19}: P1.B8 (VA20), U1.42 (A19)
/A_{20}: P1.B9 (VA21), SJ2.1 (A), SJ4.1 (A), U4.2 (A0)
/A_{21}: P1.B10 (VA22), TP1.1
/A_{22}: P1.B11 (VA23), TP2.1
/D_{0}: P1.A20 (VD0), U1.14 (D0), U2.11 (Q0), U3.2 (D)
/D_{1}: P1.A23 (VD1), U1.16 (D1), U2.12 (Q1)
/D_{2}: P1.A26 (VD2), U1.18 (D2), U2.13 (Q2)
/D_{3}: P1.A29 (VD3), U1.20 (D3), U2.15 (Q3)
/D_{4}: P1.A28 (VD4), U1.23 (D4), U2.16 (Q4)
/D_{5}: P1.A25 (VD5), U1.25 (D5), U2.17 (Q5)
/D_{6}: P1.A22 (VD6), U1.27 (D6), U2.18 (Q6)
/D_{7}: P1.A19 (VD7), U1.29 (D7), U2.19 (Q7)
/D_{8}: P1.A21 (VD8), U1.15 (D8)
/D_{9}: P1.A24 (VD9), U1.17 (D9)
/D_{10}: P1.A27 (VD10), U1.19 (D10)
/D_{11}: P1.A30 (VD11), U1.21 (D11)
/D_{12}: P1.B25 (VD12), U1.24 (D12)
/D_{13}: P1.B24 (VD13), U1.26 (D13)
/D_{14}: P1.B23 (VD14), U1.28 (D14)
/D_{15}: P1.B22 (VD15), U1.30 (D15)
/SEL: SJ3.2 (B), U3.5 (Q)
/~CE: P1.B17 (~CE), SJ5.1 (A), U4.15 (E)
/~CE_{RAM}: Q1A1.1 (E), Q1B1.2 (E), R5.1, U4.12 (O0)
/~CE_{ROM}: SJ5.2 (B), U1.11 (~CE), U4.9 (O3)
/~CE_{SRAM}: Q1A1.3 (C), Q1B1.3 (C), R4.1, U2.20 (~CS)
/~LWR: P1.B28 (~LWR), TP3.1, U2.27 (~WE)
/~OE: P1.B16 (~OE), U1.13 (~GVPP), U2.22 (~OE)
/~TIME: P1.B31 (~TIME), U3.3 (C)
/~VRES: D3.2 (A), P1.B27 (~VRES), R2.2, R3.1, U3.1 (~R)
GND: B1.2 (-), C1.2, C2.2, C3.2, C4.2, CB.2, CC.2, D10.1 (K), D11.1 (K), D12.1 (K), D13.1 (K), D14.1 (K), D15.1 (K), D16.1 (K), D17.1 (K), D18.1 (K), D19.1 (K), P1.A1 (GND), P1.A18 (GND), P1.A32 (GND), P1.B32 (~CART), R2.1, U1.12 (GND), U1.31 (GND), U2.14 (GND), U3.7 (GND), U3.10 (~S), U3.13 (~R), U4.1 (E), U4.8 (GND)
unnamed: B1.1 (+), R1.2
unnamed: D10.2 (A), R10.2
unnamed: D11.2 (A), R11.2
unnamed: D12.2 (A), R12.2
unnamed: D13.2 (A), R13.2
unnamed: D14.2 (A), R14.2
unnamed: D15.2 (A), R15.2
unnamed: D16.2 (A), R16.2
unnamed: D17.2 (A), R17.2
unnamed: D18.2 (A), R18.2
unnamed: D19.2 (A), R19.2
unnamed: Q1A1.2 (B), Q1B1.1 (B), R3.2
unnamed: SJ1.1 (A), SJ2.2 (B), U1.32 (A20)
unnamed: SJ3.1 (A), SJ4.2 (B), U4.3 (A1)
unnamed: U4.7 (O3), U4.13 (A1), U4.14 (A0)

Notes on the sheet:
ROM ≤ 2MB
27C322
ROM > 2MB
27C160

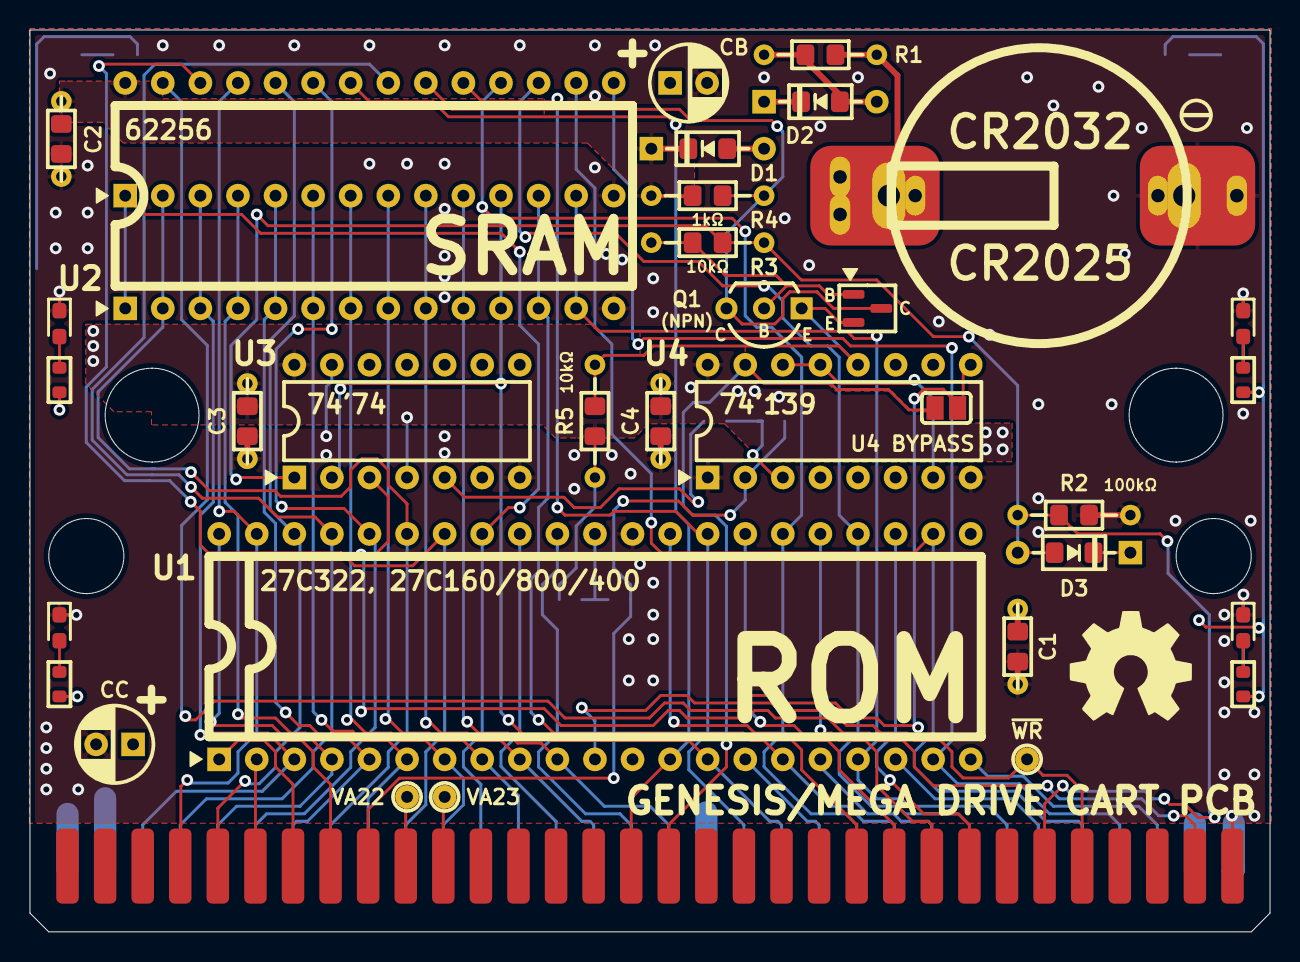
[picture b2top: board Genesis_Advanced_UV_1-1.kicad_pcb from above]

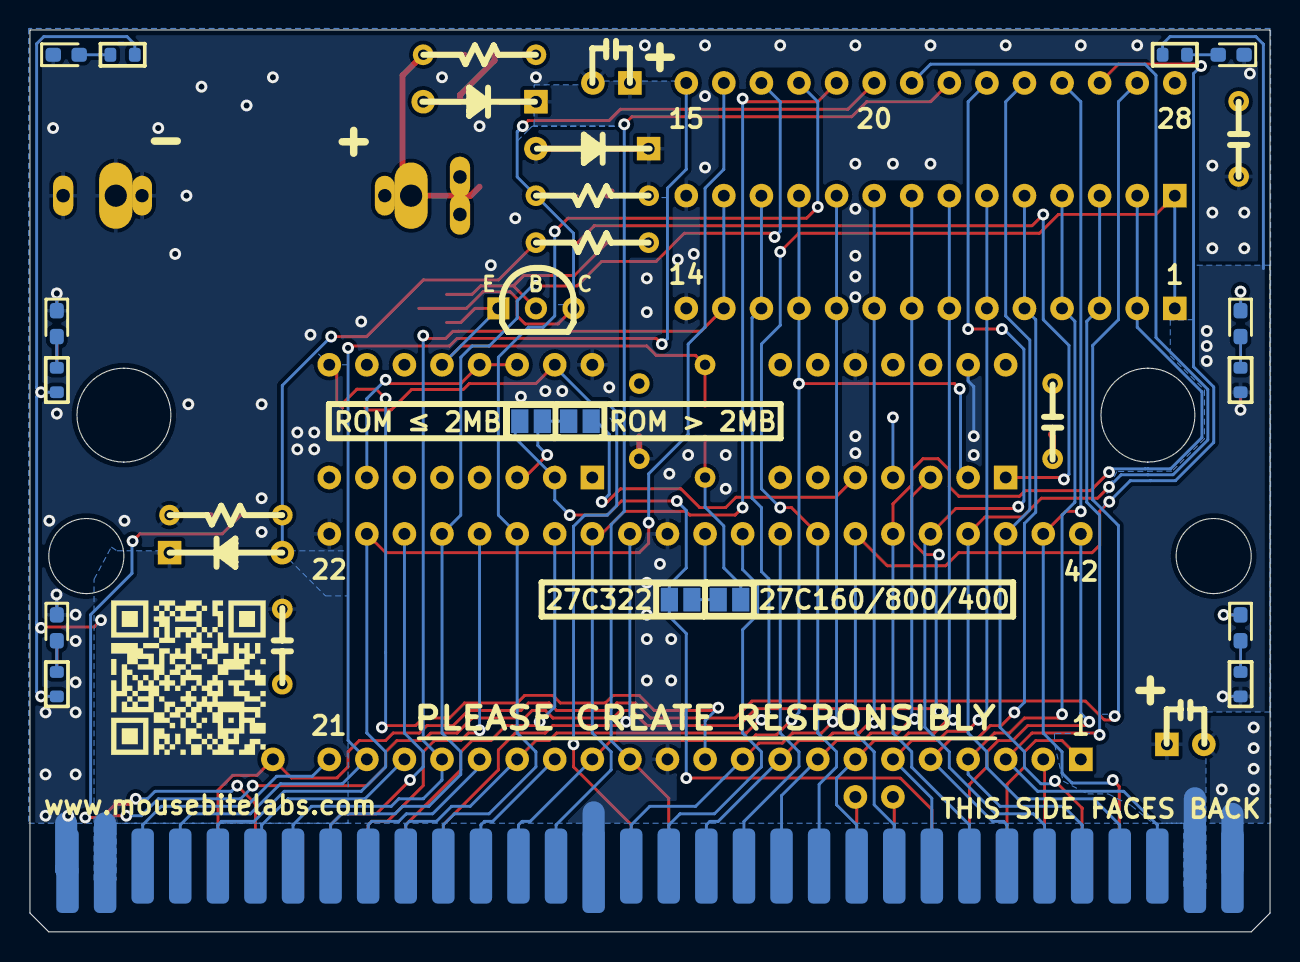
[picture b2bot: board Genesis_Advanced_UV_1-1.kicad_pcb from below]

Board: 2 copper layers, 83.8 x 61.0 mm, 50 parts (16 on the bottom side), 67 nets.

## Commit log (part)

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2025-12-15 Update README.md
    Updated coin cell part number

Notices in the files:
Advanced Flash/README.md:
This work is licensed under a Creative Commons Attribution-ShareAlike 4.0 International License. You are able to copy and redistribute the material in any medium or format, as well as remix, transform, or build upon the material for any purpose (even commercial) - but you **must** give appropriate credit, provide a link t
©MouseBiteLabs 2025
